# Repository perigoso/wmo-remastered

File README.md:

# wmo-remastered
Replacement PCB for the classic WMO (Wheel mouse Optical) by Mcrosoft

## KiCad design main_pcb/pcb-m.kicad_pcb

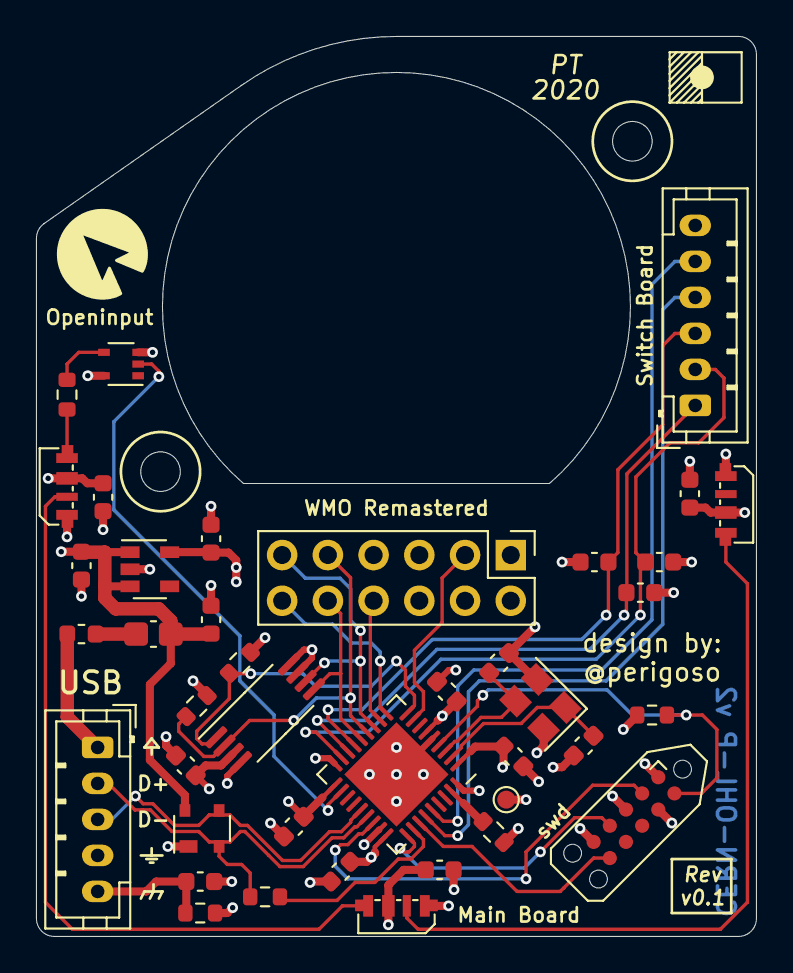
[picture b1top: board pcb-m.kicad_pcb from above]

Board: 4 copper layers, 40.0 x 50.0 mm, 40 parts (0 on the bottom side), 33 nets.

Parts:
C101, C104, C105, C106, C108, C109, C110, C111, C112, C113, C114, C115, C116, C117: 100nF; C_0603_1608Metric
C102: 10uF; C_0603_1608Metric
C103, C107: 12pF; C_0603_1608Metric
D101: PRTR5V0U2X; SOT-143
D102, D103, D104: SK6812_SIDE
F101: 500mA; Fuse_0805_2012Metric_Castellated
FB101: L_0603_1608Metric
J101: Conn_01x05; JST_PH_B5B-PH-K_1x05_P2.00mm_Vertical
J102: Conn_ARM_JTAG_SWD_10; Tag-Connect_TC2050-IDC-NL_2x05_P1.27mm_Vertical
J103: Conn_01x06; JST_PH_B6B-PH-K_1x06_P2.00mm_Vertical
J104: Conn_02x06_Odd_Even; PinHeader_2x06_P2.54mm_Vertical
R101, R102: 10k; R_0603_1608Metric
R103: 1M; R_0603_1608Metric
R104, R105: 100k; R_0603_1608Metric
R106: 100; R_0603_1608Metric
R107: 1.5k; R_0603_1608Metric
TP101: 3V3; TestPoint_Pad_D1.0mm
U101: STM32F103T8Ux; QFN-36-1EP_6x6mm_P0.5mm_EP4.1x4.1mm
U102: 25LCxxx; TSSOP-8_4.4x3mm_P0.65mm
U103: MIC5504-3.3YM5; SOT-23-5
U104: 74LVC1G17; SOT-353_SC-70-5
Y101: 12MHz; Crystal_SMD_3225-4Pin_3.2x2.5mm

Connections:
+3V3: C104.2, C105.2, C108.2, C109.2, C110.2, C111.1, J102.1, J104.1, R102.2, R104.1, TP101.1, U101.1, U101.6, U101.19, U101.27, U102.3, U102.7, U102.8, U103.5
+5V: C102.2, C106.2, C112.2, C115.2, C117.2, D101.4, D102.2, D103.2, D104.2, F101.1, U103.1, U103.3, U104.5
/BTN_L: C113.1, J103.3, U101.15
/BTN_M: C116.1, J103.1, U101.16
/BTN_R: C114.1, J103.2, U101.17
/EEPROM_MISO: J104.9, R105.1, U101.13, U102.2
/EEPROM_MOSI: J104.10, U101.14, U102.5
/EEPROM_SCLK: J104.11, U101.12, U102.6
/ENC_A: J103.4, U101.31
/ENC_B: J103.5, U101.32
/HF_XTAL_N: C107.2, U101.3, Y101.3
/HF_XTAL_P: C103.2, U101.2, Y101.1
/LED_D: U101.20, U104.2
/SENSOR_MOTION: J104.12, U101.10
/SWCLK: J102.4, U101.28
/SWDIO: J102.2, U101.25
/SWO: J102.6, U101.30
/USB_D_N: D101.3, J101.3, U101.23
/USB_D_P: D101.2, J101.2, R107.2, U101.24
/VBUS: FB101.2, J101.1
/VBUS_FUSED: F101.2, FB101.1
/~EEPROM_CS: R104.2, U101.9, U102.1
/~MCU_RESET: J102.10, R102.1, U101.4
/~SENSOR_CS: J104.8, U101.11
/~SENSOR_RESET: J104.3, U101.8
GND: C101.1, C102.1, C103.1, C104.1, C105.1, C106.1, C107.1, C108.1, C109.1, C110.1, C111.2, C112.1, C113.2, C114.2, C115.1, C116.2, C117.1, D101.1, D102.4, D103.4, D104.4, J101.4, J102.3, J102.5, J102.9, J103.6, J104.2, J104.4, J104.5, J104.6, J104.7, R101.2, R103.2, R105.2, U101.5, U101.18, U101.26, U101.36, U101.37, U102.4, U103.2, U104.3, Y101.2, Y101.4
unnamed: C101.2, J101.5, R103.1
unnamed: D102.1, R106.1
unnamed: D102.3, D103.1
unnamed: D103.3, D104.1
unnamed: R101.1, U101.35
unnamed: R106.2, U104.4
unnamed: R107.1, U101.29

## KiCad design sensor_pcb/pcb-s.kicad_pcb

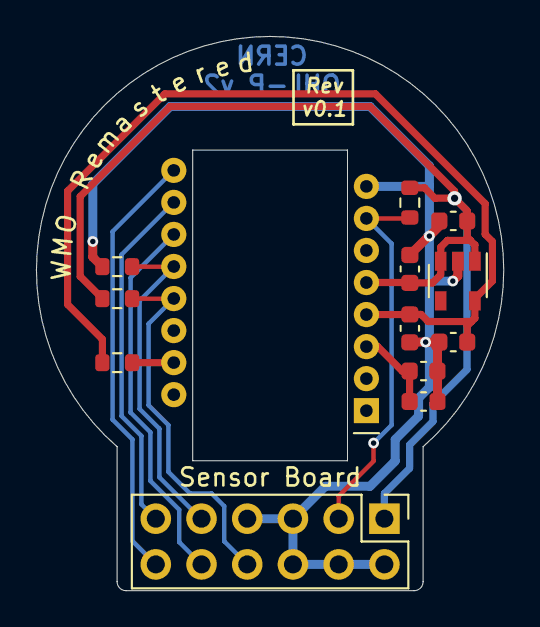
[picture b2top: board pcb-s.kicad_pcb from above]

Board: 2 copper layers, 26.0 x 30.8 mm, 13 parts (0 on the bottom side), 11 nets.

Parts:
C101, C102: 1uF; C_0603_1608Metric
C103, C104, C105: 100nF; C_0603_1608Metric
C106: 4.7uF; C_0603_1608Metric
J101: Conn_02x06_Odd_Even; PinHeader_2x06_P2.54mm_Vertical
R101, R102, R103: 100k; R_0603_1608Metric
R104: 39; R_0603_1608Metric
U101: MIC5504-1.8YM5; SOT-23-5
U102: PMW3360

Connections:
+1V8: C102.1, C105.1, R104.1, U101.5, U102.4
+3V3: C101.1, C103.1, J101.1, R101.1, R103.1, U101.1, U101.3, U102.5
/MISO: J101.9, R102.1, U102.12
/MOSI: J101.10, U102.11
/MOTION: J101.12, U102.9
/SCLK: J101.11, U102.10
/~CS: J101.8, R101.2, U102.13
/~RESET: J101.3, R103.2, U102.7
GND: C101.2, C102.2, C103.2, C104.2, C105.2, C106.2, J101.2, J101.4, J101.5, J101.6, J101.7, R102.2, U101.2, U102.8
unnamed: C104.1, C106.1, U102.3
unnamed: R104.2, U102.15

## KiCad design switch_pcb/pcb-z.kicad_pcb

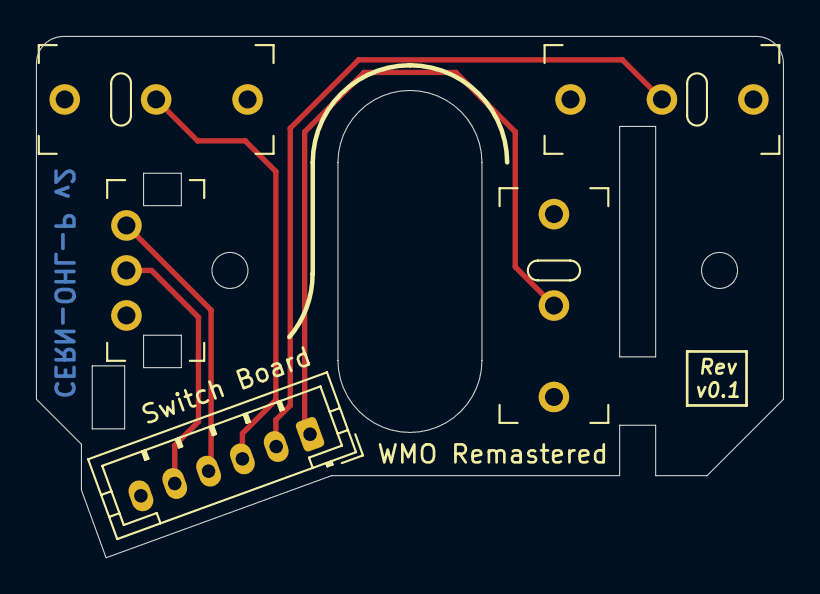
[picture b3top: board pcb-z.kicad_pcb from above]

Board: 2 copper layers, 41.5 x 29.0 mm, 5 parts (0 on the bottom side), 6 nets.

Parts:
J101: Conn_01x06; JST_PH_B6B-PH-K_1x06_P2.00mm_Vertical
SW101, SW102, SW103: SW_Push; Generic
SW104: Rotary_Encoder; Encoder

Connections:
/BTN_L: J101.3, SW101.2
/BTN_M: J101.1, SW103.2
/BTN_R: J101.2, SW102.2
/ENC_A: J101.4, SW104.A
/ENC_B: J101.5, SW104.B
GND: J101.6, SW101.1, SW102.1, SW103.1, SW104.C

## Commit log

2020-12-24 Upload Rev0.1
2020-12-24 Add transparency to assets
2020-12-24 Add main pcb edge cad

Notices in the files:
main_pcb/pcb-m.kicad_pcb:
CERN-OHL-P v2
